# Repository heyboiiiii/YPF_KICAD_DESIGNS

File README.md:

# YPF_KICAD_DESIGNS
KICAD schematics and pcbs for the computer of the "Desafio ECO YPF" Car and submodules. 

Project auto:
    computer based on esp32 and display ili9844 attached to the steering wheel.
    
Project SHIELD_LORA:
    adaptation of the module smt1278 lora to 5 pin(2.54mm header)
    
project ACS_V_placa:
    here is where are the terminals of the batteries connect to the current sensor ACS712(30A) and the voltage resistor
    
    this board will be connected to project through 3 cables.

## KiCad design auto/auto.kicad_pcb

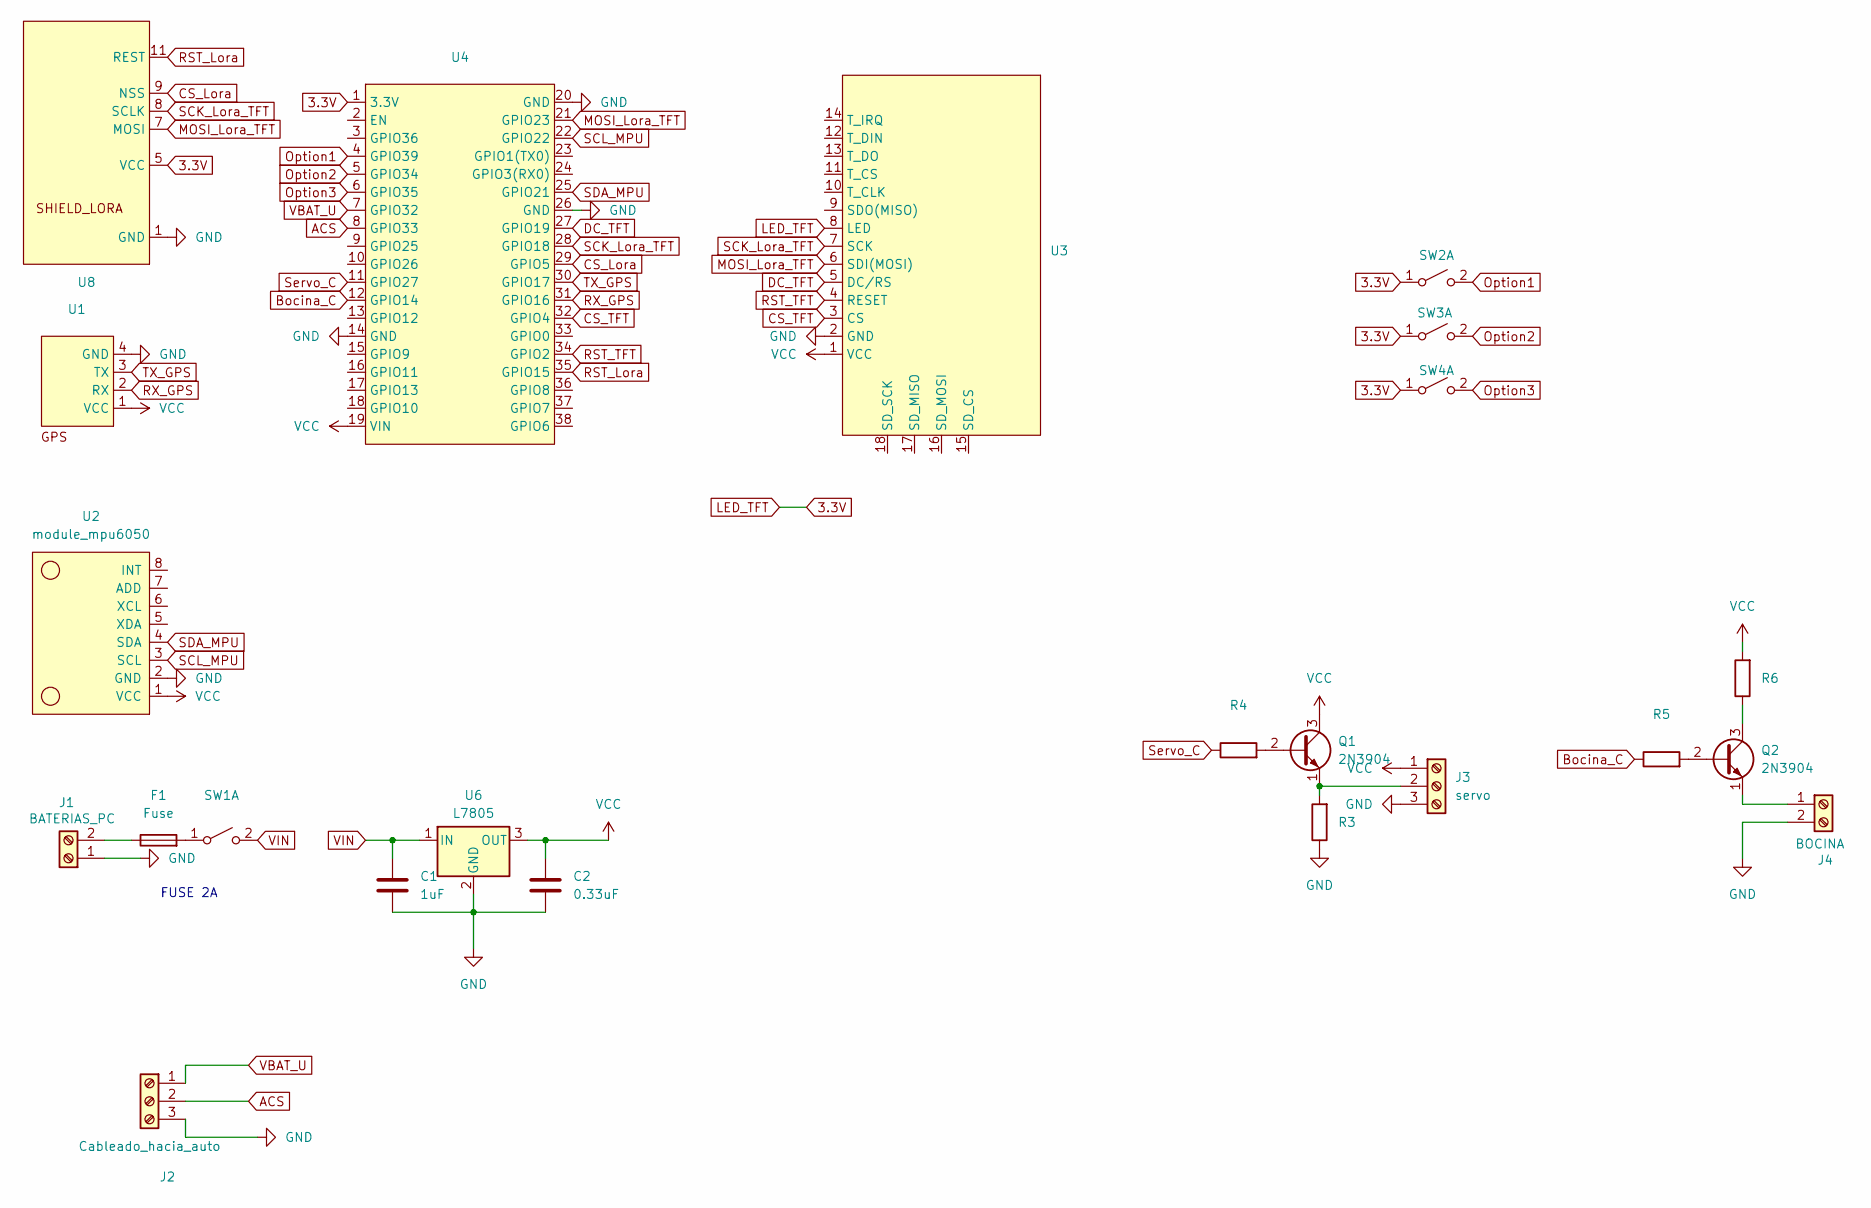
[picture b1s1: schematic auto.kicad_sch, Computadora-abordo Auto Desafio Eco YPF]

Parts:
C1: 1uF; R_Axial_DIN0204_L3.6mm_D1.6mm_P5.08mm_Horizontal
C2: 0.33uF; R_Axial_DIN0204_L3.6mm_D1.6mm_P5.08mm_Horizontal
F1: Fuse; Fuseholder_Clip-5x20mm_Littelfuse_445-030_Inline_P20.50x5.2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
J1: BATERIAS_PC; TerminalBlock_MaiXu_MX126-5.0-02P_1x02_P5.00mm
J2: Cableado_hacia_auto; TerminalBlock_MaiXu_MX126-5.0-03P_1x03_P5.00mm
J3: servo; PinHeader_1x03_P2.54mm_Vertical
J4: BOCINA; PinHeader_1x02_P2.54mm_Vertical
Q1, Q2: 2N3904; TO-92_Inline
R3, R5, R6: 10k; R_Axial_DIN0204_L3.6mm_D1.6mm_P5.08mm_Horizontal
R4: 10k; R_Axial_DIN0207_L6.3mm_D2.5mm_P10.16mm_Horizontal
SW1: SW_DPST_x2; SW_DIP_SPSTx01_Slide_6.7x4.1mm_W7.62mm_P2.54mm_LowProfile
SW2: SW1; SW_PUSH-12mm_Wuerth-430476085716
SW3, SW4: SW_DPST_x2; SW_PUSH-12mm_Wuerth-430476085716
U1: GY-NEO6MV2
U2: module_mpu6050; module_MPU6050
U3: tft_3.5_display
U4: esp32
U6: L7805; TO-220-3_Vertical
U8: SHIELD XL1278

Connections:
3.3V: SW2.1 (A), SW3.1 (A), SW4.1 (A), U3.8 (LED), U4.1 (3.3V), U8.5 (VCC)
ACS: J2.2, U4.8 (GPIO33)
Bocina_C: R5.1, U4.12 (GPIO14)
CS_Lora: U4.29 (GPIO5), U8.9 (NSS)
CS_TFT: U3.3 (CS), U4.32 (GPIO4)
DC_TFT: U3.5 (DC/RS), U4.27 (GPIO19)
GND: C1.2, C2.2, J1.1, J2.3, J3.3, J4.2, R3.1, U1.4 (GND), U2.2 (GND), U3.2 (GND), U4.14 (GND), U4.20 (GND), U4.26 (GND), U6.2 (GND), U8.1 (GND)
MOSI_Lora_TFT: U3.6 (SDI(MOSI)), U4.21 (GPIO23), U8.7 (MOSI)
unnamed: F1.1, J1.2
unnamed: J3.2, Q1.1 (E), R3.2
unnamed: J4.1, Q2.1 (E)
unnamed: Q1.2 (B), R4.2
unnamed: Q2.2 (B), R5.2
unnamed: Q2.3 (C), R6.1
unnamed: F1.2, SW1.1 (A)
Option1: SW2.2 (B), U4.4 (GPIO39)
Option2: SW3.2 (B), U4.5 (GPIO34)
Option3: SW4.2 (B), U4.6 (GPIO35)
RST_Lora: U4.35 (GPIO15), U8.11 (REST)
RST_TFT: U3.4 (RESET), U4.34 (GPIO2)
RX_GPS: U1.2 (RX), U4.31 (GPIO16)
SCK_Lora_TFT: U3.7 (SCK), U4.28 (GPIO18), U8.8 (SCLK)
SCL_MPU: U2.3 (SCL), U4.22 (GPIO22)
SDA_MPU: U2.4 (SDA), U4.25 (GPIO21)
Servo_C: R4.1, U4.11 (GPIO27)
TX_GPS: U1.3 (TX), U4.30 (GPIO17)
VBAT_U: J2.1, U4.7 (GPIO32)
VCC: C2.1, J3.1, Q1.3 (C), R6.2, U1.1 (VCC), U2.1 (VCC), U3.1 (VCC), U4.19 (VIN), U6.3 (OUT)
VIN: C1.1, SW1.2 (B), U6.1 (IN)

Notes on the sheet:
FUSE 2A

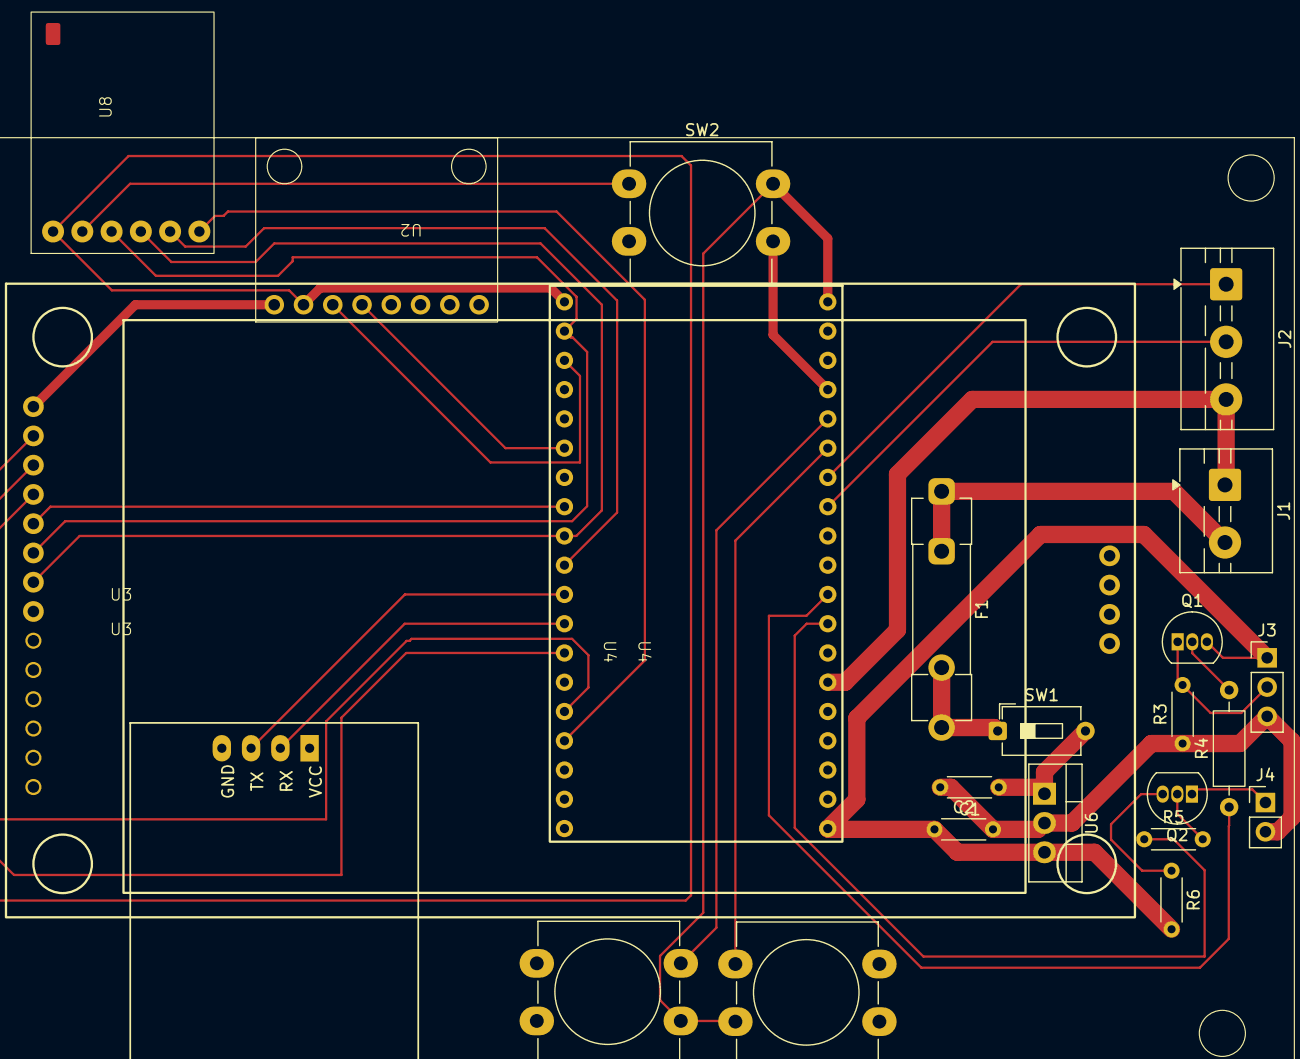
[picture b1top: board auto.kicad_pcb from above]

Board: 2 copper layers, 23 parts (0 on the bottom side), 29 nets.

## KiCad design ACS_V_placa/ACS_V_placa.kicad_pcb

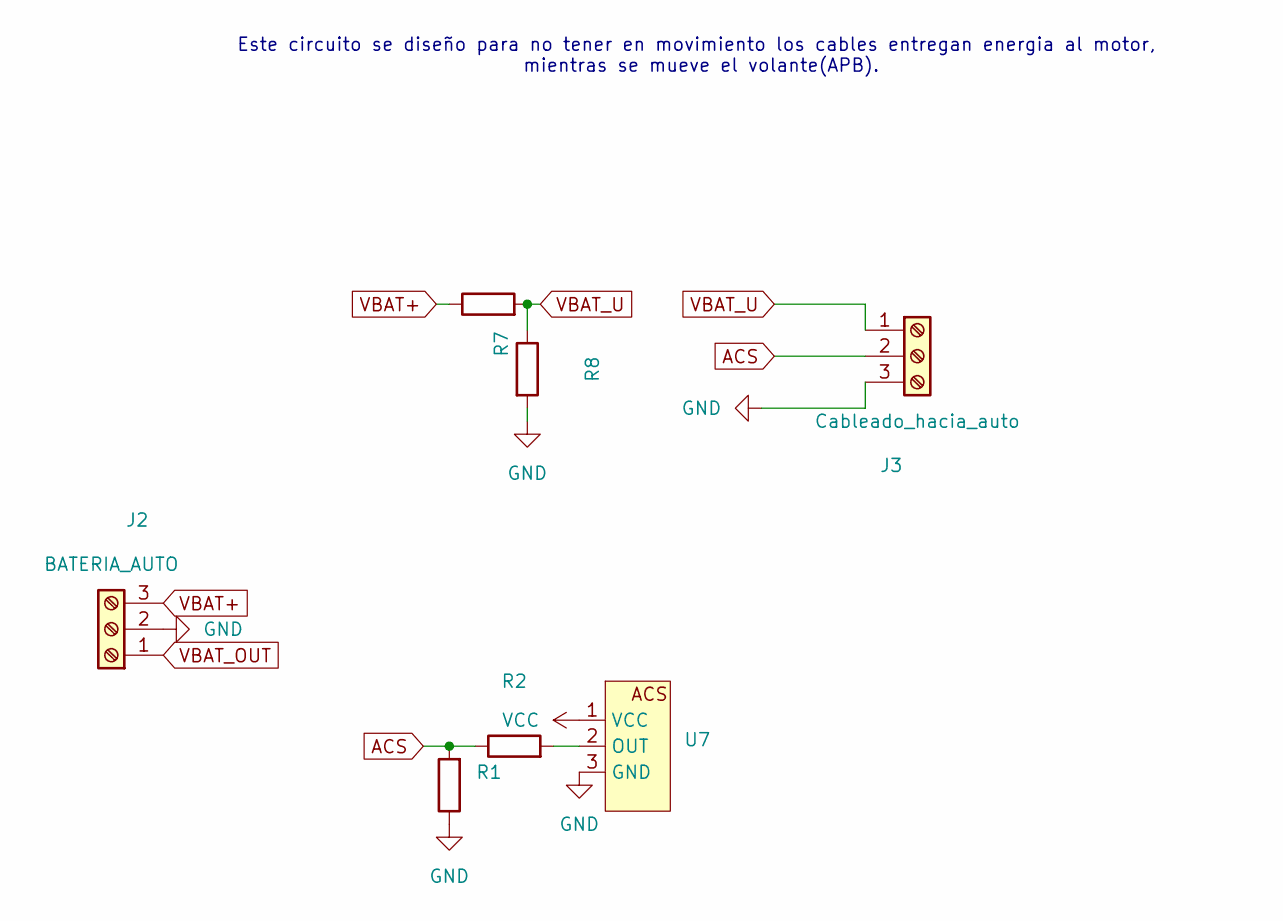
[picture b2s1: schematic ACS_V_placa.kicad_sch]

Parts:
J2: BATERIA_AUTO; teminals_bateries
J3: Cableado_hacia_auto; TerminalBlock_MaiXu_MX126-5.0-03P_1x03_P5.00mm
R1, R7: 10K; R_Axial_DIN0204_L3.6mm_D1.6mm_P5.08mm_Horizontal
R2, R8: 10k; R_Axial_DIN0204_L3.6mm_D1.6mm_P5.08mm_Horizontal
U7: PinHeader_1x03_P2.54mm_Vertical

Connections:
ACS: J3.2, R1.2, R2.1
GND: J2.2, J3.3, R1.1, R8.2, U7.3 (GND)
unnamed: R2.2, U7.2 (OUT)
VBAT+: J2.3, R7.1
VBAT_OUT: J2.1
VBAT_U: J3.1, R7.2, R8.1
VCC: U7.1 (VCC)

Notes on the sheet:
Este circuito se diseño para no tener en movimiento los cables entregan energia al motor, mientras se mueve el volante(APB).

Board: 2 copper layers, 7 parts (0 on the bottom side), 5 nets, no tracks yet.

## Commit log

2025-07-08 1 commit: esquematico hecho(REVISAR PINES), modulos PCB de acople para lora hecho.
2025-07-08 fixed schematic.
2025-07-14 esquematico(falta agregar fusible 1 / 2 A)
2025-07-17 esquematico finalizado, PCB en proceso.
